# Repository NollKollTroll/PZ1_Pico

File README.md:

# PZ1_Pico

A version of the PZ1-system based on 65C02, Raspberry Pi Pico and 512KiB SRAM.

## General info

This is the second public release of SW and HW for the PZ1-project, now with some more bells and whistles.<br>
<br>
The system uses my simple preemptive multitasking scheduler to manage the 512KiB RAM, using 16KiB for itself and system data.<br>
The task switching does not waste many cycles. Every task gets its own stack and a full zero page, minus the 18 bytes used for OS-calls.<br>
EhBASIC is running in a separate task with 64KiB RAM. There are added basic-commands to deal with tasks and the filesystem.<br>
<br>
HW realised in the Pico:<br>
- Serial communication via a virtual USB serial port.<br>
- Serial port, 3.3V RX/TX on pin-header. Working but not used.<br>
- SID-sound is based on TinySID, emulated on the second core of the Pico and mixed at 96000Hz, no SID-filters. 10-bit PWM-output on a single pin.<br>
- IRQ-timer used by the scheduler, 16-bits.<br>
- Frame counter registers, incremented @50Hz, 16-bits.<br>
- HW/SW interfaces to filesystem operations.<br>
- 4 bank registers, 16KiB memory blocks, the scheduler handles ownership of blocks.<br>
<br>
The HW design is not the most efficient, mainly because the Pico lacks enough gpios to connect to the 65C02 and SRAM without buffers. The buffering is done with 74LVC-chips which adds complexity and lowers efficiency. The Pico and buffers are cheaper and more readily available than the faster and less complex Teensy 4.1.<br>
<br>
Running the Pico at the standard 133MHz can run the 65C02 @1MHz. Overclocking the Pico to 250MHz can run the 65C02 @2MHz, just the way I intended. Using the PIOs would probably improve the performance.

## History

I started the PZ1 project because I wanted to code 6502, build proper electronics hardware and investigate multitasking and bank-switched memory on a 6502-system. I also got back to designing proper PCBs, now in KiCad. I've done some iterations experimenting with:<br>
- 6502 emulation or a real 65C02.<br>
- Different MCUs: Teensy 4.0/4.1 / BluePill / Pico.<br>
- External SRAM, RAM/ROM inside MCU, RAM on Teensy quad-SPI.<br>
- Different sound emulation and output (PWM/I2S).<br>
- 74-series glue logic / SPLD.<br>

## Blog

The ongoing work of PZ1 in general can be followed on [my blog at hackaday.io](https://hackaday.io/project/171471-pz1-6502-laptop)

## Hardware

Use KiCad 6 to view/edit the schematics and PCB. There is also a PDF of the schematics.<br>
Gerbers to build the 4-layer PCB are generated and available in a separate folder.<br>
The Pico-socket in 3D-view of the PCB is not correct, too narrow.<br>
<br>
A proper BOM is missing but here are the main components:<br>
- 1x Raspberry Pi Pico<br>
- 1x WDC65C02<br>
- 1x AS6C4008, 512KiB SRAM<br>
- 2x 74LVC244<br>
- 1x 74LVC245<br>
- 2x 74LVC373<br>
- 2x 1x6 pin-header<br>
- 2x 1x4 pin-header<br>
- 1x 1x2 pin-header<br>
- a bunch of decoupling capacitors<br>

## Software

Use Arduino IDE with Earl Philhowers Pico board package, -O2 optimization.<br>
The 6502-sources include pre-assembled h-files in the repository. Assembling on your own requires installation of the very fine assembler [Jasm](http://kollektivet.nu/jasm/).<br>
Run the asm.sh file to create the necessary h-files, along with a bunch of debug- and info-files.<br>

## Contact

Mail: <adam.klotblixt@gmail.com>

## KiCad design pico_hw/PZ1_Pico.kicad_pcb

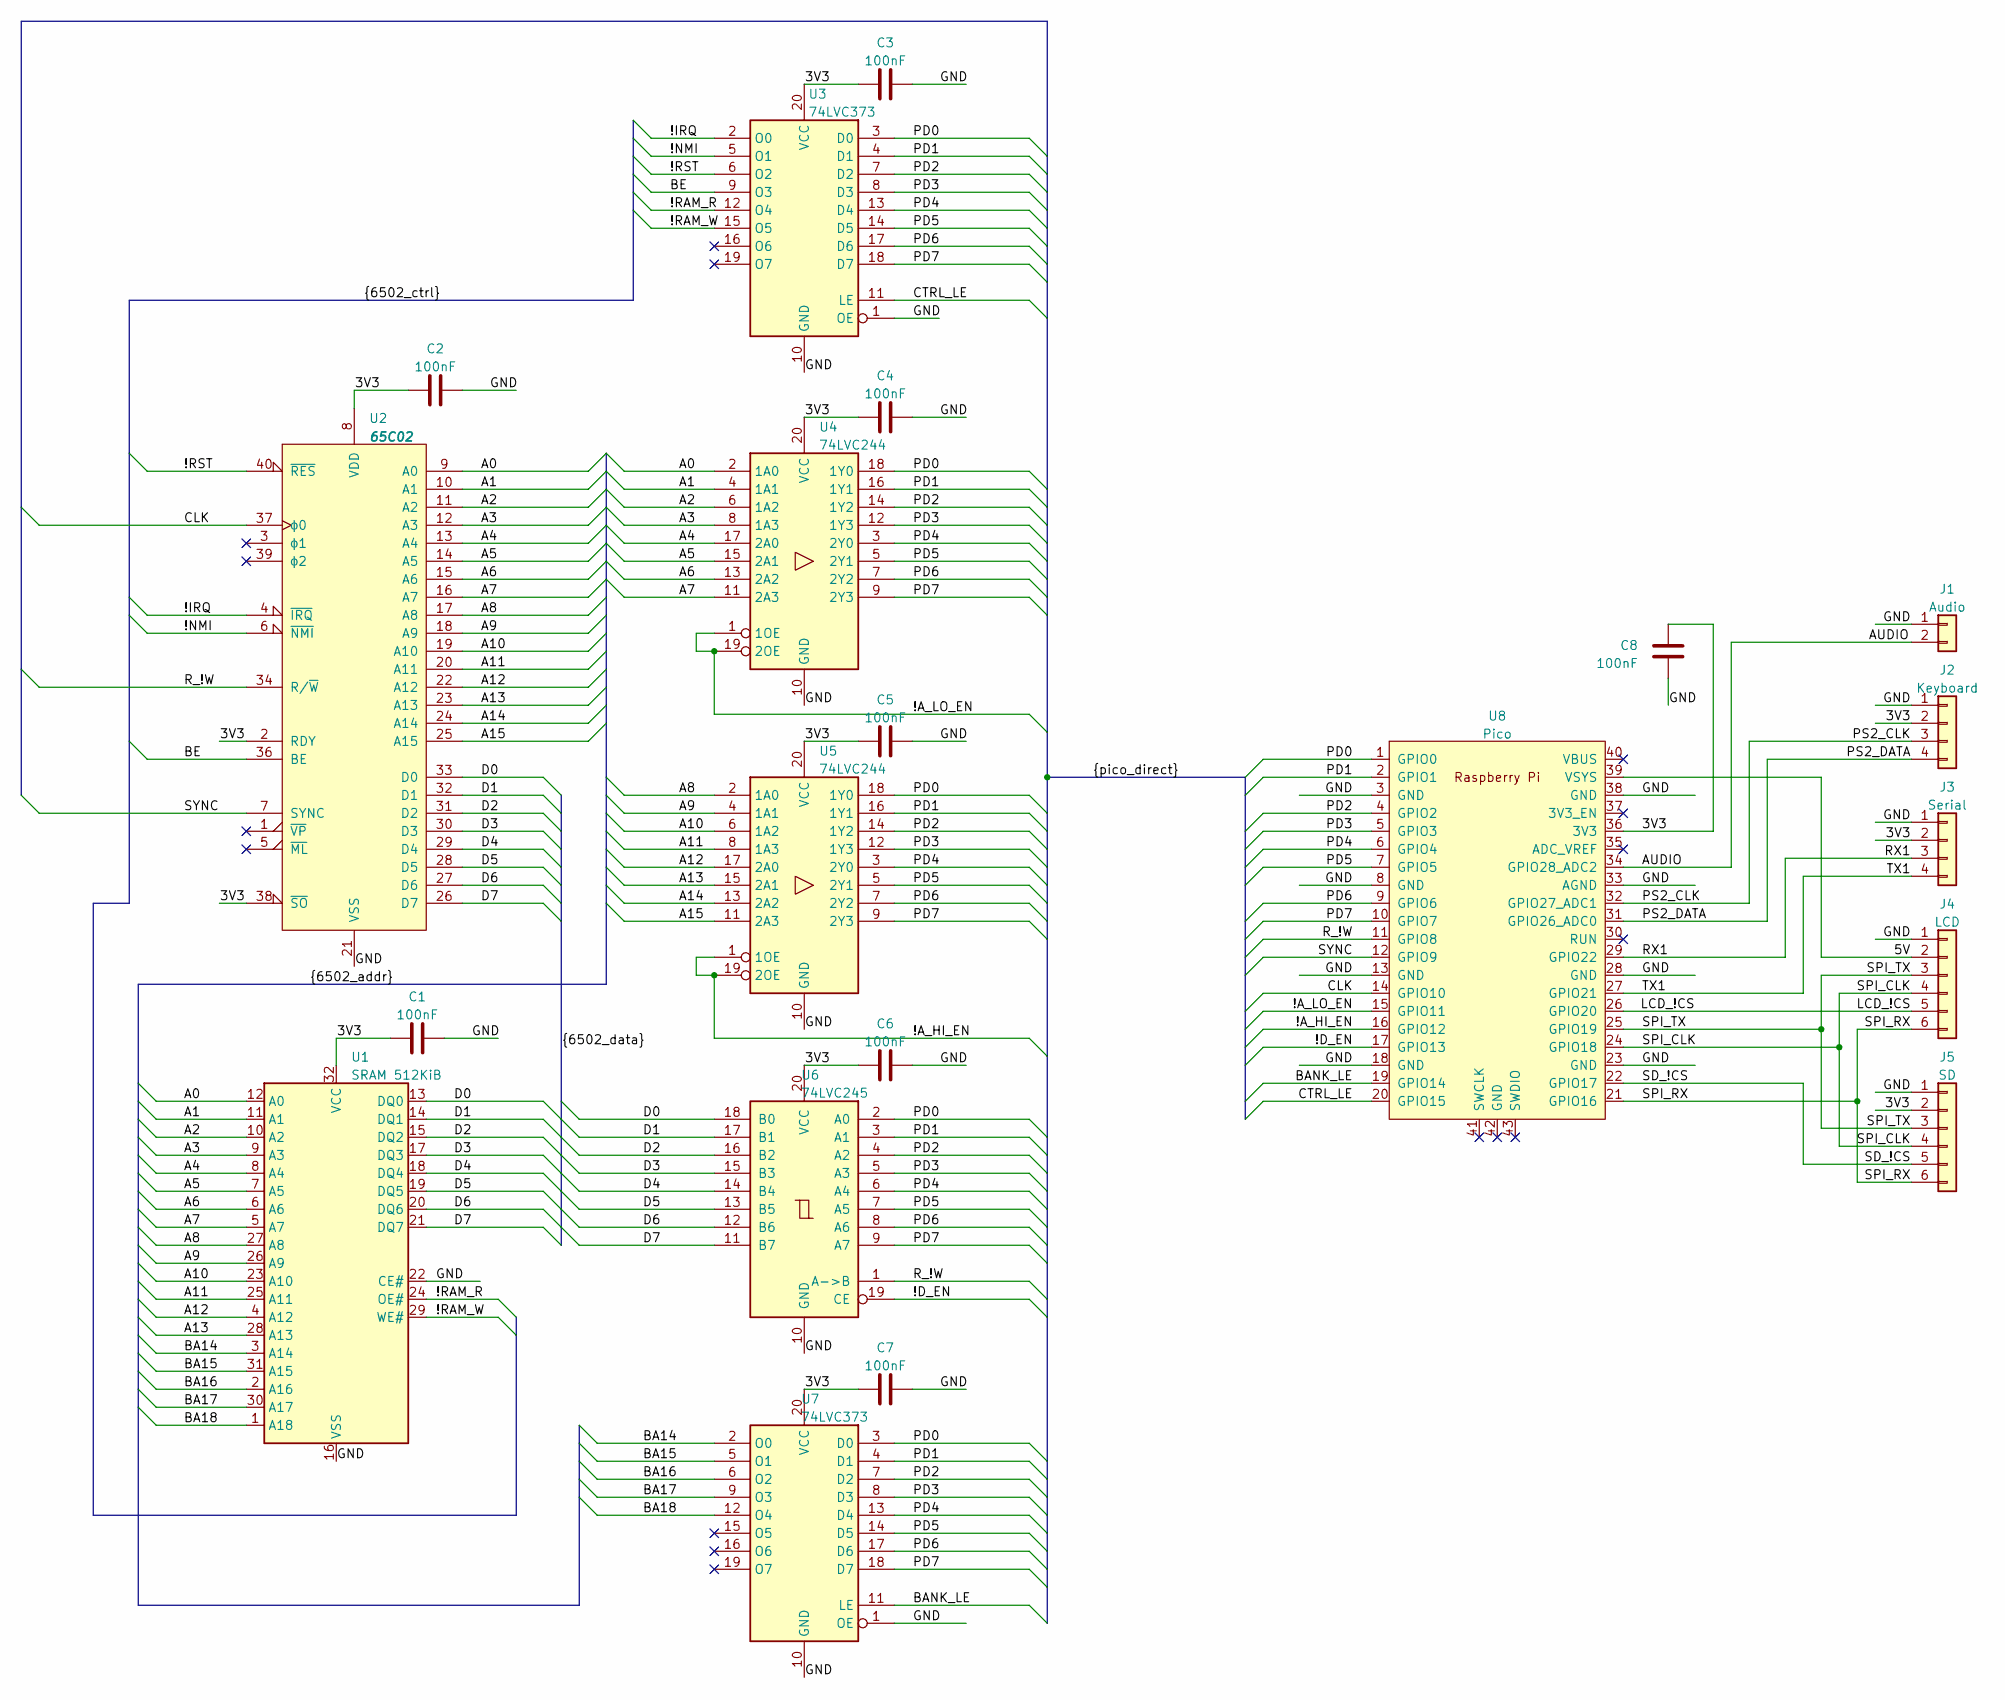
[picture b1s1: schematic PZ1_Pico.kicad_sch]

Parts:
C1, C2, C3, C4, C5, C6, C7, C8: 100nF; C_0805_2012Metric_Pad1.18x1.45mm_HandSolder
J1: Audio; PinHeader_1x02_P2.54mm_Vertical
J2: Keyboard; PinHeader_1x04_P2.54mm_Vertical
J3: Serial; PinHeader_1x04_P2.54mm_Vertical
J4: LCD; PinHeader_1x06_P2.54mm_Vertical
J5: SD; PinHeader_1x06_P2.54mm_Vertical
U1: SRAM 512KiB; DIP-32_W15.24mm
U2: 65C02; DIP-40_W15.24mm
U3, U7: 74LVC373; DIP-20_W7.62mm
U4, U5: 74LVC244; DIP-20_W7.62mm
U6: 74LVC245; DIP-20_W7.62mm
U8: Pico; DIP-40_W17.78mm_Socket

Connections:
/3V3: C1.1, C2.1, C3.1, C4.1, C5.1, C6.1, C7.1, C8.2, J2.2, J3.2, J5.2, U1.32 (VCC), U2.2 (RDY), U2.8 (VDD), U2.38 (~SO), U3.20 (VCC), U4.20 (VCC), U5.20 (VCC), U6.20 (VCC), U7.20 (VCC), U8.36 (3V3)
/5V: J4.2, U8.39 (VSYS)
/!A_HI_EN: U5.1 (1OE), U5.19 (2OE), U8.16 (GPIO12)
/!A_LO_EN: U4.1 (1OE), U4.19 (2OE), U8.15 (GPIO11)
/!D_EN: U6.19 (CE), U8.17 (GPIO13)
/!IRQ: U2.4 (~IRQ), U3.2 (O0)
/!NMI: U2.6 (~NMI), U3.5 (O1)
/!RAM_R: U1.24 (OE#), U3.12 (O4)
/!RAM_W: U1.29 (WE#), U3.15 (O5)
/!RST: U2.40 (~RES), U3.6 (O2)
/A0: U1.12 (A0), U2.9 (A0), U4.2 (1A0)
/A1: U1.11 (A1), U2.10 (A1), U4.4 (1A1)
/A2: U1.10 (A2), U2.11 (A2), U4.6 (1A2)
/A3: U1.9 (A3), U2.12 (A3), U4.8 (1A3)
/A4: U1.8 (A4), U2.13 (A4), U4.17 (2A0)
/A5: U1.7 (A5), U2.14 (A5), U4.15 (2A1)
/A6: U1.6 (A6), U2.15 (A6), U4.13 (2A2)
/A7: U1.5 (A7), U2.16 (A7), U4.11 (2A3)
/A8: U1.27 (A8), U2.17 (A8), U5.2 (1A0)
/A9: U1.26 (A9), U2.18 (A9), U5.4 (1A1)
/A10: U1.23 (A10), U2.19 (A10), U5.6 (1A2)
/A11: U1.25 (A11), U2.20 (A11), U5.8 (1A3)
/A12: U1.4 (A12), U2.22 (A12), U5.17 (2A0)
/A13: U1.28 (A13), U2.23 (A13), U5.15 (2A1)
/A14: U2.24 (A14), U5.13 (2A2)
/A15: U2.25 (A15), U5.11 (2A3)
/AUDIO: J1.2, U8.34 (GPIO28_ADC2)
/BA14: U1.3 (A14), U7.2 (O0)
/BA15: U1.31 (A15), U7.5 (O1)
/BA16: U1.2 (A16), U7.6 (O2)
/BA17: U1.30 (A17), U7.9 (O3)
/BA18: U1.1 (A18), U7.12 (O4)
/BANK_LE: U7.11 (LE), U8.19 (GPIO14)
/BE: U2.36 (BE), U3.9 (O3)
/CLK: U2.37 (ϕ0), U8.14 (GPIO10)
/CTRL_LE: U3.11 (LE), U8.20 (GPIO15)
/D0: U1.13 (DQ0), U2.33 (D0), U6.18 (B0)
/D1: U1.14 (DQ1), U2.32 (D1), U6.17 (B1)
/D2: U1.15 (DQ2), U2.31 (D2), U6.16 (B2)
/D3: U1.17 (DQ3), U2.30 (D3), U6.15 (B3)
/D4: U1.18 (DQ4), U2.29 (D4), U6.14 (B4)
/D5: U1.19 (DQ5), U2.28 (D5), U6.13 (B5)
/D6: U1.20 (DQ6), U2.27 (D6), U6.12 (B6)
/D7: U1.21 (DQ7), U2.26 (D7), U6.11 (B7)
/GND: C1.2, C2.2, C3.2, C4.2, C5.2, C6.2, C7.2, C8.1, J1.1, J2.1, J3.1, J4.1, J5.1, U1.16 (VSS), U1.22 (CE#), U2.21 (VSS), U3.1 (OE), U3.10 (GND), U4.10 (GND), U5.10 (GND), U6.10 (GND), U7.1 (OE), U7.10 (GND), U8.3 (GND), U8.8 (GND), U8.13 (GND), U8.18 (GND), U8.23 (GND), U8.28 (GND), U8.33 (AGND), U8.38 (GND)
/LCD_!CS: J4.5, U8.26 (GPIO20)
/PD0: U3.3 (D0), U4.18 (1Y0), U5.18 (1Y0), U6.2 (A0), U7.3 (D0), U8.1 (GPIO0)
/PD1: U3.4 (D1), U4.16 (1Y1), U5.16 (1Y1), U6.3 (A1), U7.4 (D1), U8.2 (GPIO1)
/PD2: U3.7 (D2), U4.14 (1Y2), U5.14 (1Y2), U6.4 (A2), U7.7 (D2), U8.4 (GPIO2)
/PD3: U3.8 (D3), U4.12 (1Y3), U5.12 (1Y3), U6.5 (A3), U7.8 (D3), U8.5 (GPIO3)
/PD4: U3.13 (D4), U4.3 (2Y0), U5.3 (2Y0), U6.6 (A4), U7.13 (D4), U8.6 (GPIO4)
/PD5: U3.14 (D5), U4.5 (2Y1), U5.5 (2Y1), U6.7 (A5), U7.14 (D5), U8.7 (GPIO5)
/PD6: U3.17 (D6), U4.7 (2Y2), U5.7 (2Y2), U6.8 (A6), U7.17 (D6), U8.9 (GPIO6)
/PD7: U3.18 (D7), U4.9 (2Y3), U5.9 (2Y3), U6.9 (A7), U7.18 (D7), U8.10 (GPIO7)
/PS2_CLK: J2.3, U8.32 (GPIO27_ADC1)
/PS2_DATA: J2.4, U8.31 (GPIO26_ADC0)
/RX1: J3.3, U8.29 (GPIO22)
/R_!W: U2.34 (R/~W), U6.1 (A->B), U8.11 (GPIO8)
/SD_!CS: J5.5, U8.22 (GPIO17)
/SPI_CLK: J4.4, J5.4, U8.24 (GPIO18)
/SPI_RX: J4.6, J5.6, U8.21 (GPIO16)
/SPI_TX: J4.3, J5.3, U8.25 (GPIO19)
/SYNC: U2.7 (SYNC), U8.12 (GPIO9)
/TX1: J3.4, U8.27 (GPIO21)

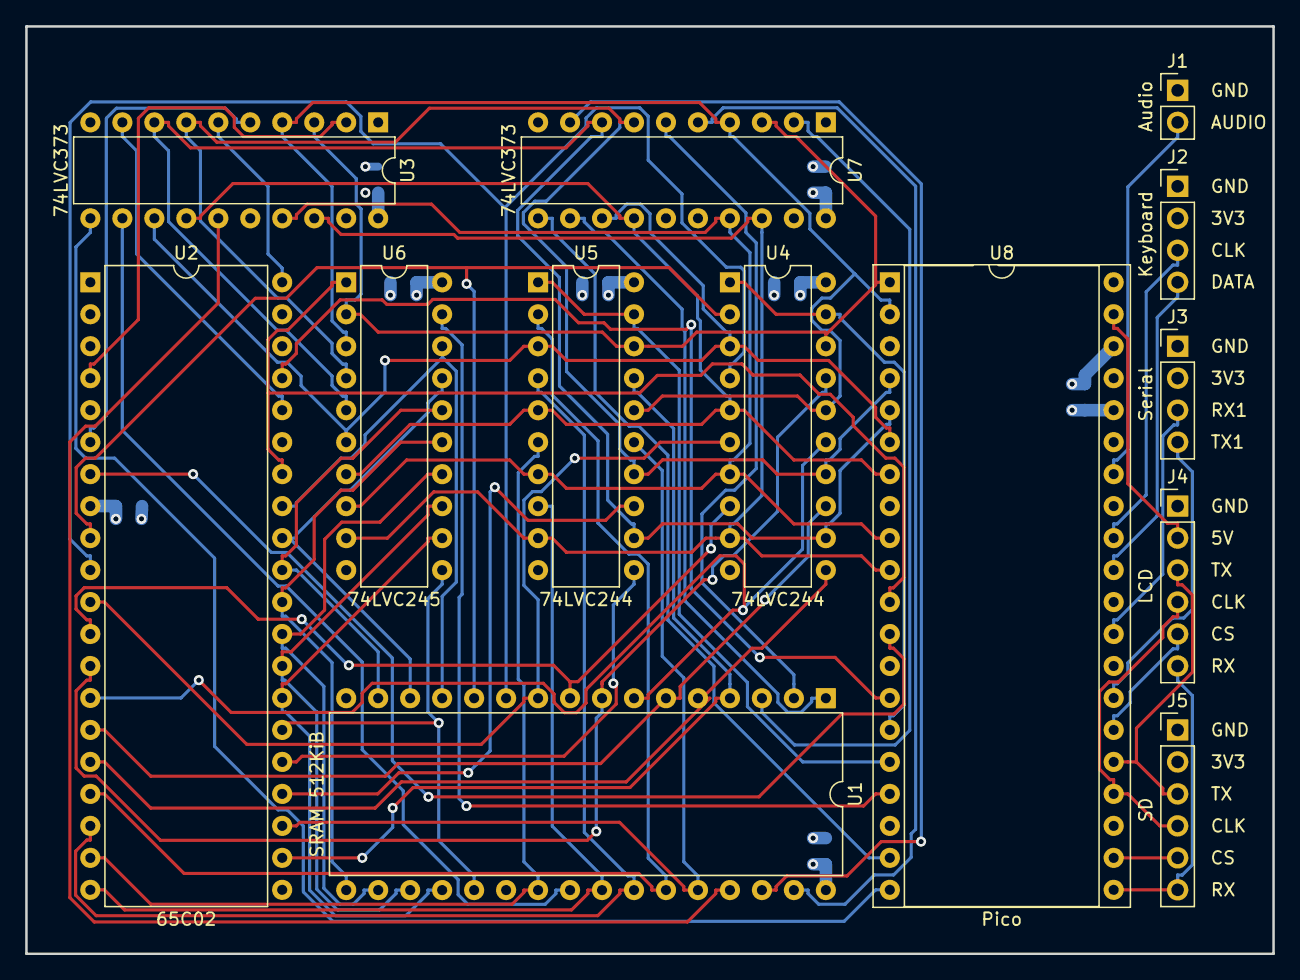
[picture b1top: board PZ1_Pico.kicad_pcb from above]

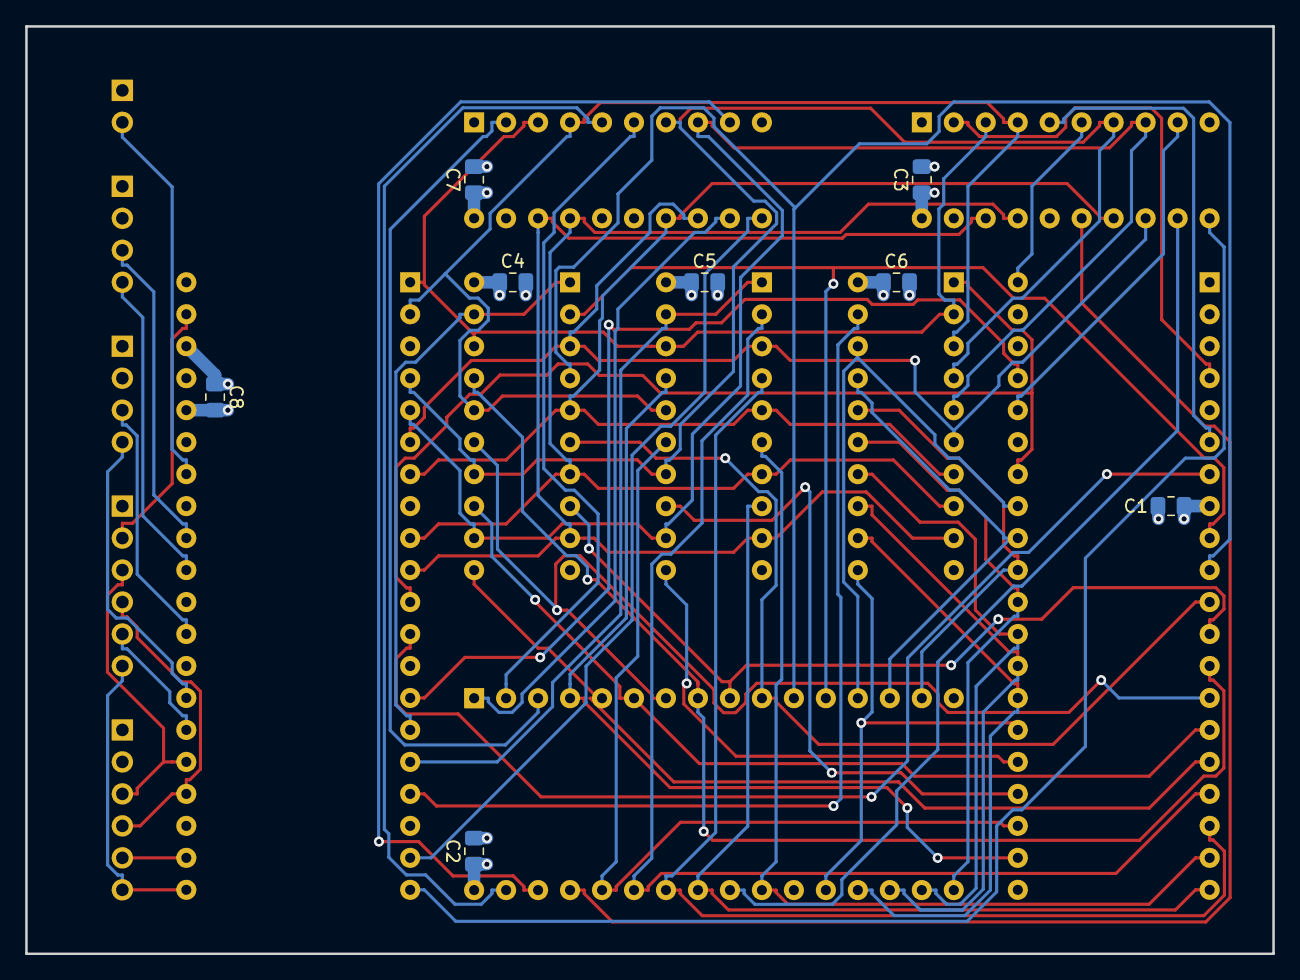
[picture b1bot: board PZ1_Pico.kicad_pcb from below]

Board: 4 copper layers, 99.1 x 73.7 mm, 21 parts (8 on the bottom side), 64 nets.

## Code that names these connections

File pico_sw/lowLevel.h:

/*
Written in 2022 by Adam Klotblixt (adam.klotblixt@gmail.com)

To the extent possible under law, the author have dedicated all
copyright and related and neighboring rights to this software to the
public domain worldwide.
This software is distributed without any warranty.

You should have received a copy of the CC0 Public Domain Dedication
along with this software. If not, see
<http://creativecommons.org/publicdomain/zero/1.0/>.
*/

#ifndef LOWLEVEL_H
#define LOWLEVEL_H

// system characteristics
#define CPU_FREQUENCY  1000000 //Hz
#define FRAME_RATE     50 //Hz
#define FRAME_TIME_US  (1000000 / FRAME_RATE)
#define SAMPLE_RATE    96000 //Hz

// SID registers
#define PORT_SID_00           0xFE00
#define PORT_SID_01           0xFE01
#define PORT_SID_02           0xFE02
#define PORT_SID_03           0xFE03
#define PORT_SID_04           0xFE04
#define PORT_SID_05           0xFE05
#define PORT_SID_06           0xFE06
#define PORT_SID_07           0xFE07
#define PORT_SID_08           0xFE08
#define PORT_SID_09           0xFE09
#define PORT_SID_0A           0xFE0A
#define PORT_SID_0B           0xFE0B
#define PORT_SID_0C           0xFE0C
#define PORT_SID_0D           0xFE0D
#define PORT_SID_0E           0xFE0E
#define PORT_SID_0F           0xFE0F
#define PORT_SID_10           0xFE10
#define PORT_SID_11           0xFE11
#define PORT_SID_12           0xFE12
#define PORT_SID_13           0xFE13
#define PORT_SID_14           0xFE14
#define PORT_SID_15           0xFE15
#define PORT_SID_16           0xFE16
#define PORT_SID_17           0xFE17
#define PORT_SID_18           0xFE18
#define PORT_SID_19           0xFE19
#define PORT_SID_1A           0xFE1A
#define PORT_SID_1B           0xFE1B
#define PORT_SID_1C           0xFE1C
// bank registers
#define PORT_BANK_0           0xFE20
#define PORT_BANK_1           0xFE21
#define PORT_BANK_2           0xFE22
#define PORT_BANK_3           0xFE23
// serial port registers
#define PORT_SERIAL_0_FLAGS   0xFE30 //bit 7: out-buffer full, bit 6: in-data available
#define PORT_SERIAL_0_IN      0xFE31
#define PORT_SERIAL_0_OUT     0xFE32
// frame counter registers
#define PORT_FRAME_COUNTER_LO 0xFE40
#define PORT_FRAME_COUNTER_HI 0xFE41
// file system registers
#define PORT_FILE_CMD         0xFE60
#define PORT_FILE_DATA        0xFE61
#define PORT_FILE_STATUS      0xFE62
// IRQ timer port registers
#define PORT_IRQ_TIMER_LO     0xFE80  //writing the lo-value fills the intermediate register
#define PORT_IRQ_TIMER_HI     0xFE81  //writing the hi-value sets the timer from the completed intermediate register
#define PORT_IRQ_TIMER_RESET  0xFE82  //timer = 0 so it can count a full cycle again
#define PORT_IRQ_TIMER_TRIG   0xFE83  //timer = max timer-value, so it triggers an irq
#define PORT_IRQ_TIMER_PAUSE  0xFE84  //pause the timer indefinitely
#define PORT_IRQ_TIMER_CONT   0xFE85  //continue the timer after a pause, also acks a triggered timer
uint8_t portMem6502[256];

// pin definitions
#define PD0            0
#define PD1            1
#define PD2            2
#define PD3            3
#define PD4            4
#define PD5            5
#define PD6            6
#define PD7            7
#define RW             8
#define SYNC           9
#define CLK            10
#define A_LO_EN_N      11
#define A_HI_EN_N      12
#define D_EN_N         13
#define BANK_LE        14
#define CTRL_LE        15
#define SPI_RX         16
#define SD_CS_N        17
#define SPI_CLK        18
#define SPI_TX         19
#define LCD_CS_N       20
#define LED_PIN        25
#define AUDIO_PIN      28
// ctrl-port
#define CTRL_IRQ_N     1
#define CTRL_NMI_N     2
#define CTRL_RST_N     4
#define CTRL_BE        8
#define CTRL_RAM_R_N   16
#define CTRL_RAM_W_N   32
uint8_t ctrlValue;

int32_t frameTimer;
uint16_t frameCounter;

#define wait1() gpio_get(LED_PIN)

static inline void setBank(uint8_t value) 
{
    gpio_set_dir_out_masked(255);
    gpio_put_masked(255, value);
    gpio_put(BANK_LE, HIGH);
    gpio_put(BANK_LE, LOW);  
}

static inline void setCtrl(uint8_t value) 
{
    gpio_set_dir_out_masked(255);
    gpio_put_masked(255, value);
    gpio_put(CTRL_LE, HIGH);
    gpio_put(CTRL_LE, LOW);  
}

static inline void setCtrlFast(uint8_t value) 
{   //WARNING: only use if the pins are already outputs, to save some time
    //gpio_set_dir_out_masked(255);
    gpio_put_masked(255, value);
    gpio_put(CTRL_LE, HIGH);
    gpio_put(CTRL_LE, LOW);   
}

static inline uint16_t getAddr() 
{
    uint16_t value;
    gpio_set_dir_in_masked(255);
    gpio_put(A_HI_EN_N, LOW);
    wait1();
    wait1();
    wait1();
    #ifdef PICO_250_MHZ
    wait1();
    #endif
    value = (gpio_get_all() & 255) << 8;
    gpio_put(A_HI_EN_N, HIGH);      
    gpio_put(A_LO_EN_N, LOW);
    wait1();
    wait1();
    wait1();
    #ifdef PICO_250_MHZ
    wait1();
    #endif
    value = value | (gpio_get_all() & 255);
    gpio_put(A_LO_EN_N, HIGH);      
    return value;
}

static inline uint8_t getData() 
{
    uint8_t value;    
    gpio_set_dir_in_masked(255);
    gpio_put(D_EN_N, LOW);
    wait1();
    wait1();
    wait1();
    #ifdef PICO_250_MHZ
    wait1();
    #endif
    value = gpio_get_all() & 255;
    gpio_put(D_EN_N, HIGH);  
    return value;
}

static inline void setDataAndClk(uint8_t value) 
{
    gpio_set_dir_out_masked(255);
    gpio_put_masked(255, value);
    gpio_put(D_EN_N, LOW);
    #ifdef PICO_250_MHZ
    wait1();
    #endif
    gpio_put(CLK, LOW);    
    gpio_put(D_EN_N, HIGH);
}

void reset6502() 
{
    ctrlValue = 255 & ~CTRL_RST_N;
    setCtrl(ctrlValue);
    busy_wait_us_32(1);
    for (int i = 0; i < 16; i++)
    {
        gpio_put(CLK, HIGH);
        busy_wait_us_32(1);
        gpio_put(CLK, LOW);
        busy_wait_us_32(1);
    }
    ctrlValue = ctrlValue | CTRL_RST_N;
    setCtrl(ctrlValue);
}

#endif //LOWLEVEL_H

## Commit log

2022-06-25 First public release, as simple as possible
2022-06-25 Added licenses and a more substantial README
2022-06-26 Added SID, IRQ-timer, frameCounter. Cleaned up low level stuff. Can run 133MHz or 250MHz.
2022-06-28 Many new ports implemented
2022-06-28 ROM is also banked now, SID is calculated
2022-07-15 comments
2022-07-15 Mega-update for threaded scheduler and EhBasic, lots of new HW.
2022-07-16 Fixing timings for 133/250 MHz
2022-07-16 Yield in SID-player works now!
2022-07-16 Use second core for audio, mix @96kHz
2022-07-16 -O2 compiles better with 2-core, audio @96kHz
2022-07-17 Moved setBank for better timing
2022-07-17 Slight update of readme
2022-07-17 Added forgotten scheduler.h
2022-07-18 Changed memory interface, single gpio. Faster.
    Instead of using MEM_RN & MEM_W_N in ctrl-register, a single gpio pin is
    used to control read/write of external RAM.
    New connection:
    RAM 22 - Pico 12 (previously unused SYNC)
    RAM 24 - RAM 16 (GND)
    RAM 29 - 65C02 34 (R/W)
2022-07-18 Changed bank-/serial-/SID-address to improve performance.
2022-07-20 Small clean-ups
2022-07-27 Changed license to CC0 on SW and HW, see LICENSE for details.
2022-07-27 Moved HW-related files to separate folder.
